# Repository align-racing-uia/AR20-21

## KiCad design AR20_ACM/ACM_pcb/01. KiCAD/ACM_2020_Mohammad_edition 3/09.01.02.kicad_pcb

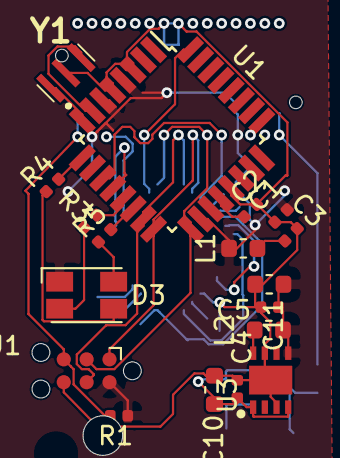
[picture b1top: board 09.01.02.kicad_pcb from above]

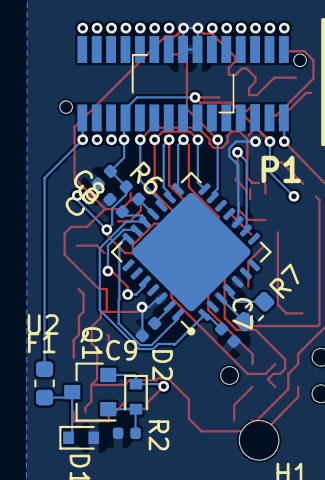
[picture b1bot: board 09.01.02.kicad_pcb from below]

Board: 2 copper layers, 32 parts (14 on the bottom side), 31 nets.

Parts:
C1, C2, C3, C4, C5, C6, C7, C8, C9: 0.1uF; C_0402_1005Metric
C10, C11: 10uF; C_0603_1608Metric
D1: 15V; D_SOD-523
D2: 2.4V; D_SOD-523
D3: ASMB-MTB0-0A3A2; LED_Avago_PLCC4_3.2x2.8mm_CW
F1: 250mA; Fuse_0603_1608Metric
H1: M2 Mouting hole; MountingHole_2.2mm_M2
J1: TC2030-MCP-NL; Tag-Connect_TC2030-IDC-NL_2x03_P1.27mm_Vertical
L1: 10uH; L_0603_1608Metric
L2: 2.2 µH; L_0603_1608Metric
P1: Conn_02x15_Odd_Even; ILWX10SBVFBE
Q1: Q_PMOS_DGS; SOT-23
R1, R6: 10K Ohm; R_0402_1005Metric
R2: 100K Ohm; R_0402_1005Metric
R3: 290 ohm; R_0402_1005Metric
R4: 200ohm; R_0402_1005Metric
R5: 190 Ohm; R_0402_1005Metric
R7: 120 Ohm; R_0603_1608Metric
U1: ATmega328P-AU; TQFP-32_7x7mm_P0.8mm
U2: MCP25625-x-SS; QFN-28-1EP_6x6mm_P0.65mm_EP4.8x4.8mm
U3: NCV890430MW50TXG; SON65P300X300X100-9N
Y1: 16.0Mhz; CSTNE16M0V530000R0

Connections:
+5V: C1.1, C5.1, C6.1, C11.1, D3.1, J1.2, L1.1, L2.2, P1.7, R1.1, R6.2, U1.4, U1.6, U1.18, U3.5
+12V: F1.2, P1.1
+12V_Safe: C4.1, C10.1, D2.1, Q1.2, U3.1, U3.4
/BLUE_LED: R5.2, U1.14
/CAN_CS: U1.11, U2.17
/CAN_INT: U1.32, U2.13
/CLK_MCP: U1.12, U2.9
/GREEN_LED: R4.2, U1.9
/MISO: J1.1, U1.16, U2.16
/MOSI: J1.4, U1.15, U2.15
/RED_LED: R3.2, U1.13
/Reset: J1.5, P1.29, R1.2
/SCK: J1.3, U1.17, U2.14
/U-Pin1: R7.2, U2.3
/U-Pin3: R7.1, U2.4
GND: C1.2, C2.2, C3.1, C4.2, C5.2, C6.2, C7.2, C8.2, C9.1, C10.2, C11.2, D1.2, J1.6, P1.16, P1.18, R2.2, U1.3, U1.5, U1.21, U2.5, U2.10, U2.26, U3.3, U3.7, U3.9, Y1.2
unnamed: C2.1, U1.20
unnamed: C3.2, L1.2
unnamed: C7.1, C8.1, U2.1, U2.19
unnamed: C9.2, U2.27
unnamed: D1.1, F1.1, Q1.3
unnamed: D2.2, Q1.1, R2.1
unnamed: D3.2, R5.1
unnamed: D3.3, R4.1
unnamed: D3.4, R3.1
unnamed: L2.1, U3.8
unnamed: R6.1, U2.18
unnamed: U1.7, Y1.3
unnamed: U1.8, Y1.1
unnamed: U2.20, U2.24
unnamed: U2.21, U2.28
